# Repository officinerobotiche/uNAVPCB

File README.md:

# ![Officine Robotiche][Logo] &micro;Nav PCB
**The first DC motor board in 4cm X 4cm** - PCB boards for &micro;Nav

This is a project in development by [Officine Robotiche] team, the check info at [official &micro;Nav site](http://unav.officinerobotiche.it/).

Feel free to ask for help, submit suggestions, satisfy your curiosity on our [**Users Group**](https://groups.google.com/forum/?hl=it#!forum/unav-users)

###Join on open firmware project [uNAV.X](https://github.com/officinerobotiche/uNAV.X)!!!

# Hardware features
- 2 DC motor control (external encoders and double H-bridge are required)
- size: 4cm x 4cm
- Matrix board with holes 2.54mm compliant
- Free 256Kb EEPROM in I2C 
- Voltage input *(Max 23V to 6V)*
- 2 internal regulators:
  - External input -> 5V
  - 5V -> 3.3V
- 4 LEDs
- ICSP programming

## DC Motor control
- 2 PWM outputs to control the speed of the motors
- Encoder input. *You can select 5V input or 3.3V to power on your encoders*: 
  - 2 channels (A, B)
  - 3 channels (A, B and Z axis)
- Analog input for current sensing
- Analog input for temperature sensing
- Pin to enable H-Bridge

## Communications
- 2 serial ports
- 1 I2C port
- 7 GP I/O (You can add feature remapping pins) 
 
# Available Shields
- [&micro;Bridge](https://github.com/officinerobotiche/uBridgePCB)

# Graphical tool for PID tuning
- [uNav_PID_Tuner](https://github.com/officinerobotiche/uNav_PID_Tuner)

[Officine Robotiche]:http://www.officinerobotiche.it/
[Logo]:http://2014.officinerobotiche.it/wp-content/uploads/sites/4/2014/09/ORlogoSimpleSmall.png

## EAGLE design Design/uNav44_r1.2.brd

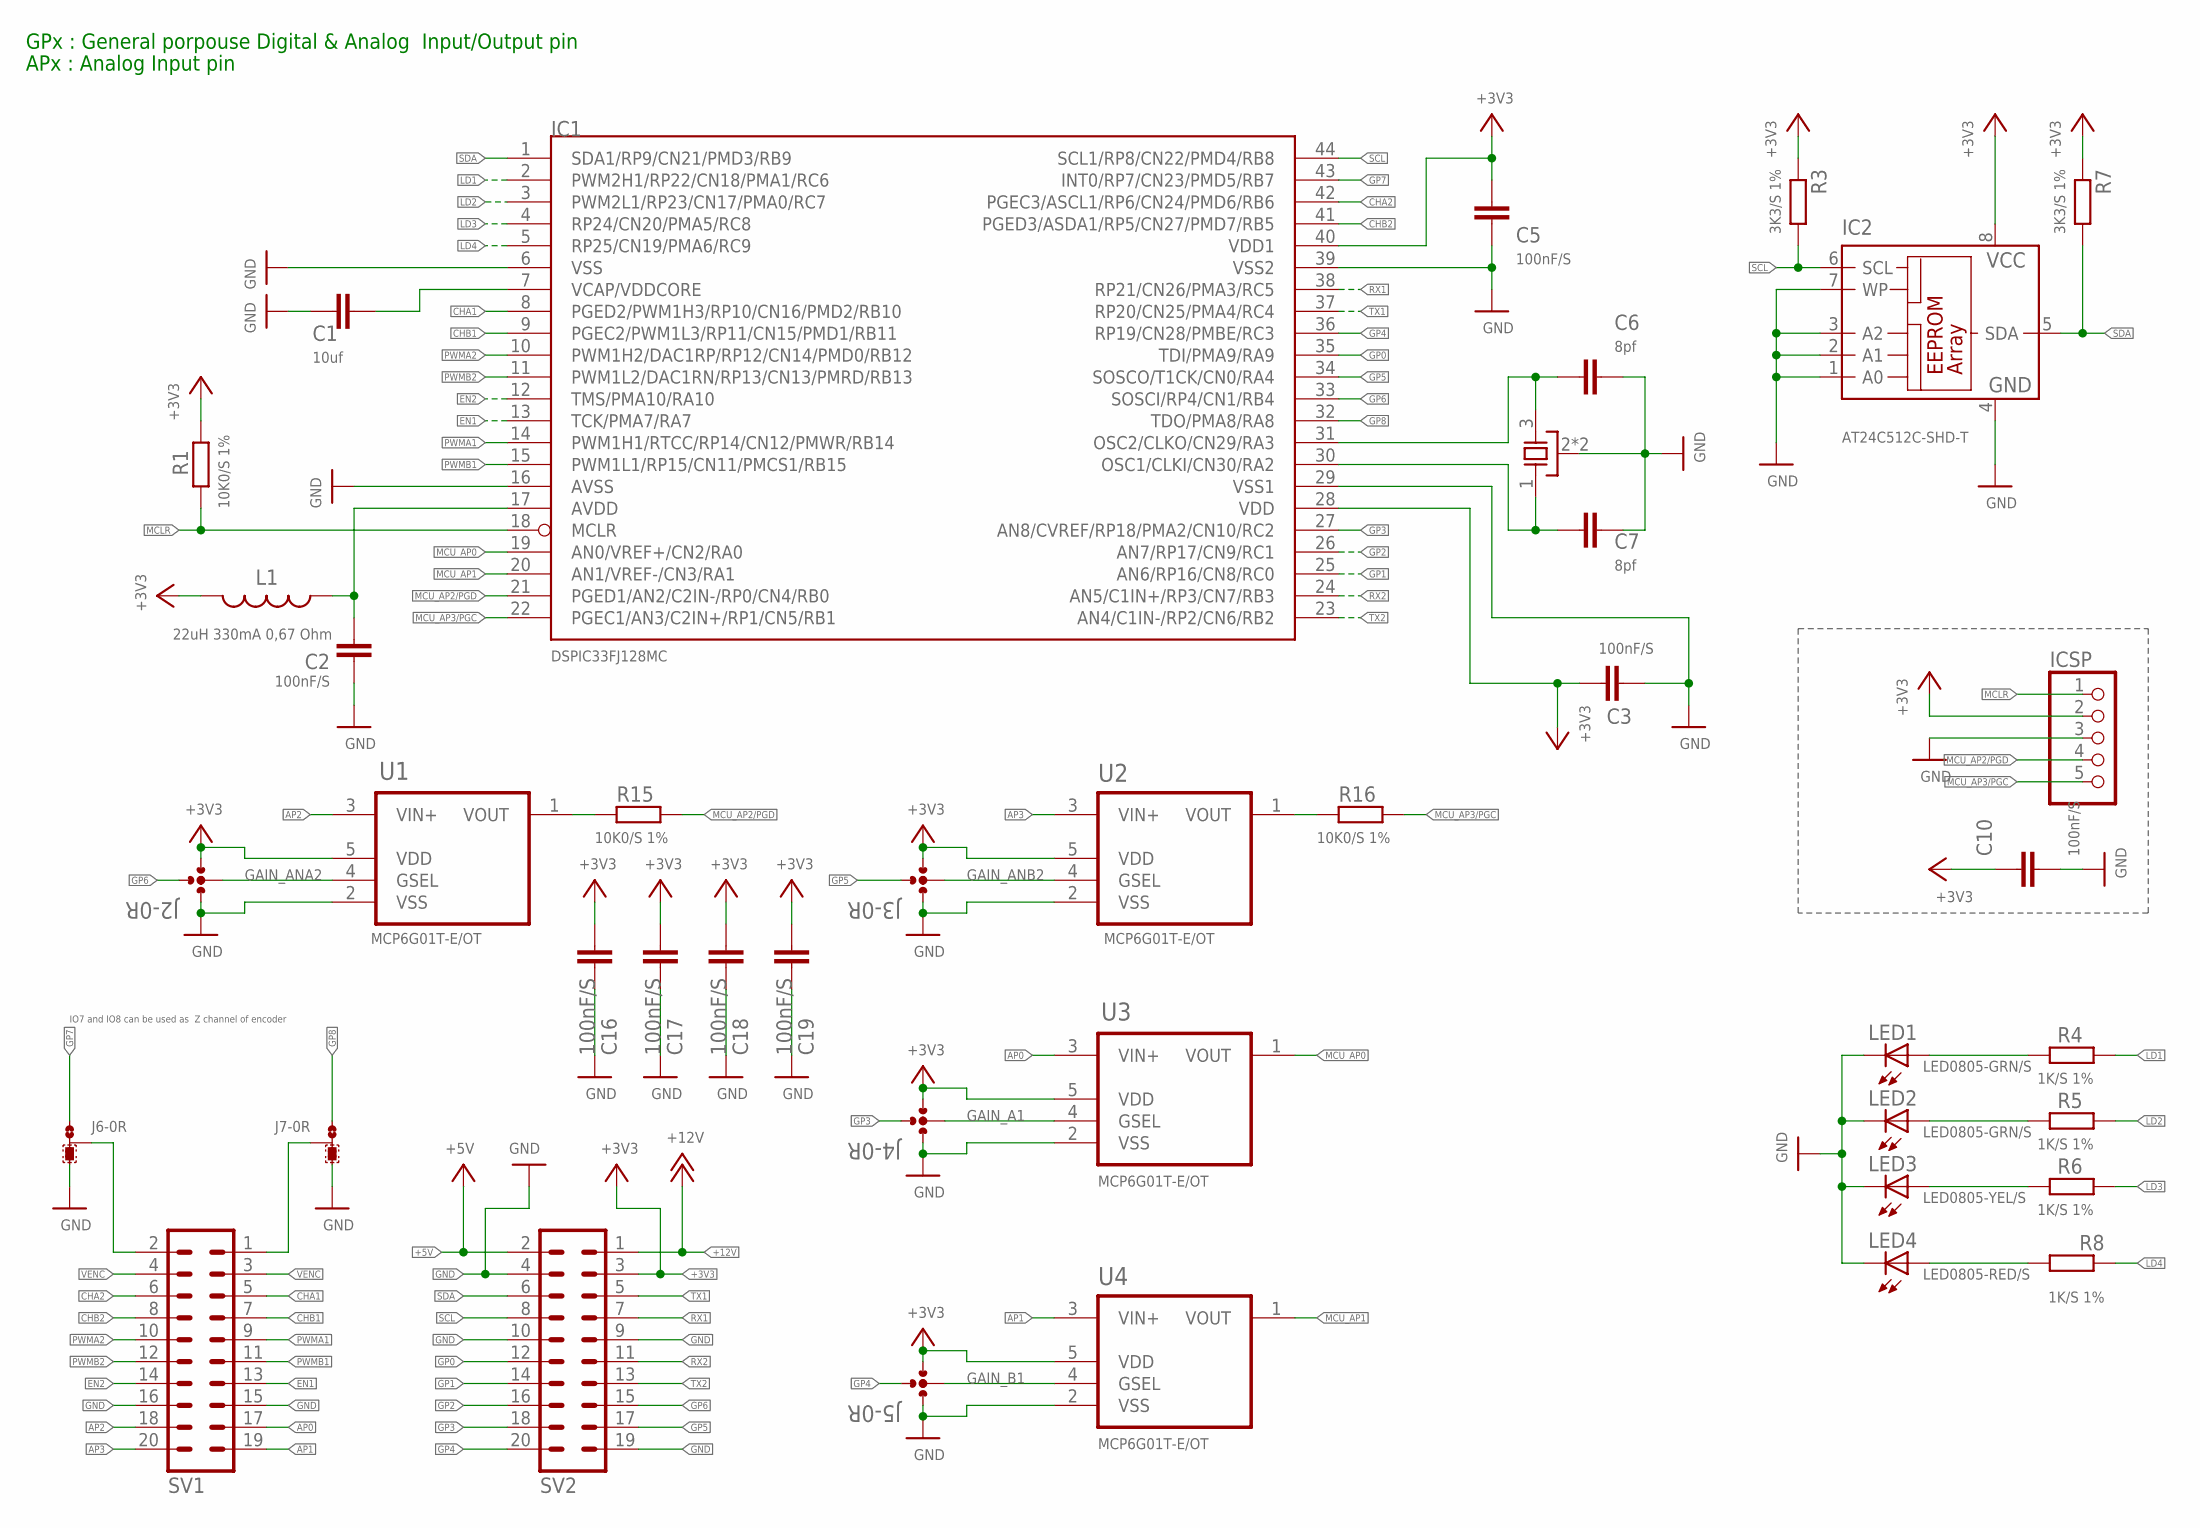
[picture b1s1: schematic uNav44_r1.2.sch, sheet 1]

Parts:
C1: 10uf; C1206
C2, C3, C5, C10, C16, C17, C18, C19: 100nF/S; C0603
C6, C7: 8pf; C0603
IC1: DSPIC33FJ128MC; TQFP44
IC2: AT24C512C-SHD-T; SO-08M
ICSP: PINHD-1X05_2.54-S; 1X05-S
J2, J3, J4, J5: 0R-JUMP-4; C0R-JUMP-4
J6, J7: 0R-JUMPC; C0R-JMP
L1: 22uH 330mA 0,67 Ohm; 0805
LED1, LED2: LED0805-GRN/S; CHIPLED_0805
LED3: LED0805-YEL/S; CHIPLED_0805
LED4: LED0805-RED/S; CHIPLED_0805
R1, R15, R16: 10K0/S 1%; R0603
R3, R7: 3K3/S 1%; R0603
R4, R5, R6, R8: 1K/S 1%; R0603
SV1, SV2: MA10-2
U1, U2, U3, U4: MCP6G01T-E/OT; SOT95P300X145-5N
XT1: 10Mhz 8pf SMD 3,20x2,50; CTS_32X25

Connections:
+3V3: C3.1, C5.2, C10.1, C16.1, C17.1, C18.1, C19.1, IC1.28 (VDD), IC1.40 (VDD1), IC2.8 (VCC), ICSP.2, J2.1, J3.1, J4.1, J5.1, L1.2, R1.2, R3.1, R7.1, SV2.3, U1.5 (VDD), U2.5 (VDD), U3.5 (VDD), U4.5 (VDD); also elsewhere on the board
+5V: SV2.2; also elsewhere on the board
+12V: SV2.1; also elsewhere on the board
AP0: SV1.17, U3.3 (VIN+)
AP1: SV1.19, U4.3 (VIN+)
AP2: SV1.18, U1.3 (VIN+)
AP3: SV1.20, U2.3 (VIN+)
AVDD: C2.2, IC1.17 (AVDD), L1.1
CHA1: IC1.8 (PGED2/PWM1H3/RP10/CN16/PMD2/RB10), SV1.5
CHA2: IC1.42 (PGEC3/ASCL1/RP6/CN24/PMD6/RB6), SV1.6
CHB1: IC1.9 (PGEC2/PWM1L3/RP11/CN15/PMD1/RB11), SV1.7
CHB2: IC1.41 (PGED3/ASDA1/RP5/CN27/PMD7/RB5), SV1.8
EN1: IC1.13 (TCK/PMA7/RA7), SV1.13
EN2: IC1.12 (TMS/PMA10/RA10), SV1.14
GAIN_A1: J4.2, U3.4 (GSEL)
GAIN_ANA2: J2.2, U1.4 (GSEL)
GAIN_ANB2: J3.2, U2.4 (GSEL)
GAIN_B1: J5.2, U4.4 (GSEL)
GND: C1.2, C2.1, C3.2, C5.1, C6.2, C7.1, C10.2, C16.2, C17.2, C18.2, C19.2, IC1.6 (VSS), IC1.16 (AVSS), IC1.29 (VSS1), IC1.39 (VSS2), IC2.1 (A0), IC2.2 (A1), IC2.3 (A2), IC2.4 (GND), IC2.7 (WP), ICSP.3, J2.3, J3.3, J4.3, J5.3, J6.3, J7.3, LED1.C, LED2.C, LED3.C, LED4.C, SV1.15, SV1.16, SV2.4, SV2.9, SV2.10, SV2.19, U1.2 (VSS), U2.2 (VSS), U3.2 (VSS), U4.2 (VSS), XT1.2 (GND), XT1.4 (GND); also elsewhere on the board
GP0: IC1.35 (TDI/PMA9/RA9), SV2.12
GP1: IC1.25 (AN6/RP16/CN8/RC0), SV2.14
GP2: IC1.26 (AN7/RP17/CN9/RC1), SV2.16
GP3: IC1.27 (AN8/CVREF/RP18/PMA2/CN10/RC2), J4.4, SV2.18
GP4: IC1.36 (RP19/CN28/PMBE/RC3), J5.4, SV2.20
GP5: IC1.34 (SOSCO/T1CK/CN0/RA4), J3.4, SV2.17
GP6: IC1.33 (SOSCI/RP4/CN1/RB4), J2.4, SV2.15
GP7: IC1.43 (INT0/RP7/CN23/PMD5/RB7), J6.1
GP8: IC1.32 (TDO/PMA8/RA8), J7.1
LD1: IC1.2 (PWM2H1/RP22/CN18/PMA1/RC6), R4.1
LD2: IC1.3 (PWM2L1/RP23/CN17/PMA0/RC7), R5.1
LD3: IC1.4 (RP24/CN20/PMA5/RC8), R6.1
LD4: IC1.5 (RP25/CN19/PMA6/RC9), R8.1
MCLR: IC1.18 (MCLR), ICSP.1, R1.1
MCU_AP0: IC1.19 (AN0/VREF+/CN2/RA0), U3.1 (VOUT)
MCU_AP1: IC1.20 (AN1/VREF-/CN3/RA1), U4.1 (VOUT)
MCU_AP2/PGD: IC1.21 (PGED1/AN2/C2IN-/RP0/CN4/RB0), ICSP.4, R15.1
MCU_AP3/PGC: IC1.22 (PGEC1/AN3/C2IN+/RP1/CN5/RB1), ICSP.5, R16.1
unnamed: C7.2, IC1.30 (OSC1/CLKI/CN30/RA2), XT1.1 (X1)
unnamed: C6.1, IC1.31 (OSC2/CLKO/CN29/RA3), XT1.3 (X2)
unnamed: J6.2, SV1.2
unnamed: LED1.A, R4.2
unnamed: LED2.A, R5.2
unnamed: R15.2, U1.1 (VOUT)
unnamed: R16.2, U2.1 (VOUT)
unnamed: J7.2, SV1.1
PWMA1: IC1.14 (PWM1H1/RTCC/RP14/CN12/PMWR/RB14), SV1.9
PWMA2: IC1.10 (PWM1H2/DAC1RP/RP12/CN14/PMD0/RB12), SV1.10
PWMB1: IC1.15 (PWM1L1/RP15/CN11/PMCS1/RB15), SV1.11
PWMB2: IC1.11 (PWM1L2/DAC1RN/RP13/CN13/PMRD/RB13), SV1.12
RX1: IC1.38 (RP21/CN26/PMA3/RC5), SV2.7
RX2: IC1.24 (AN5/C1IN+/RP3/CN7/RB3), SV2.11
SCL: IC1.44 (SCL1/RP8/CN22/PMD4/RB8), IC2.6 (SCL), R3.2, SV2.8
SDA: IC1.1 (SDA1/RP9/CN21/PMD3/RB9), IC2.5 (SDA), R7.2, SV2.6
TX1: IC1.37 (RP20/CN25/PMA4/RC4), SV2.5
TX2: IC1.23 (AN4/C1IN-/RP2/CN6/RB2), SV2.13
VCAP/VDDCORE: C1.1, IC1.7 (VCAP/VDDCORE)
VENC: SV1.3, SV1.4; also elsewhere on the board
VENC1-LD3: LED3.A, R6.2
VENC2-LD4: LED4.A, R8.2

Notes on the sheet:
IO7 and IO8 can be used as Z channel of encoder
GPx : General porpouse Digital & Analog Input/Output pin
APx : Analog Input pin

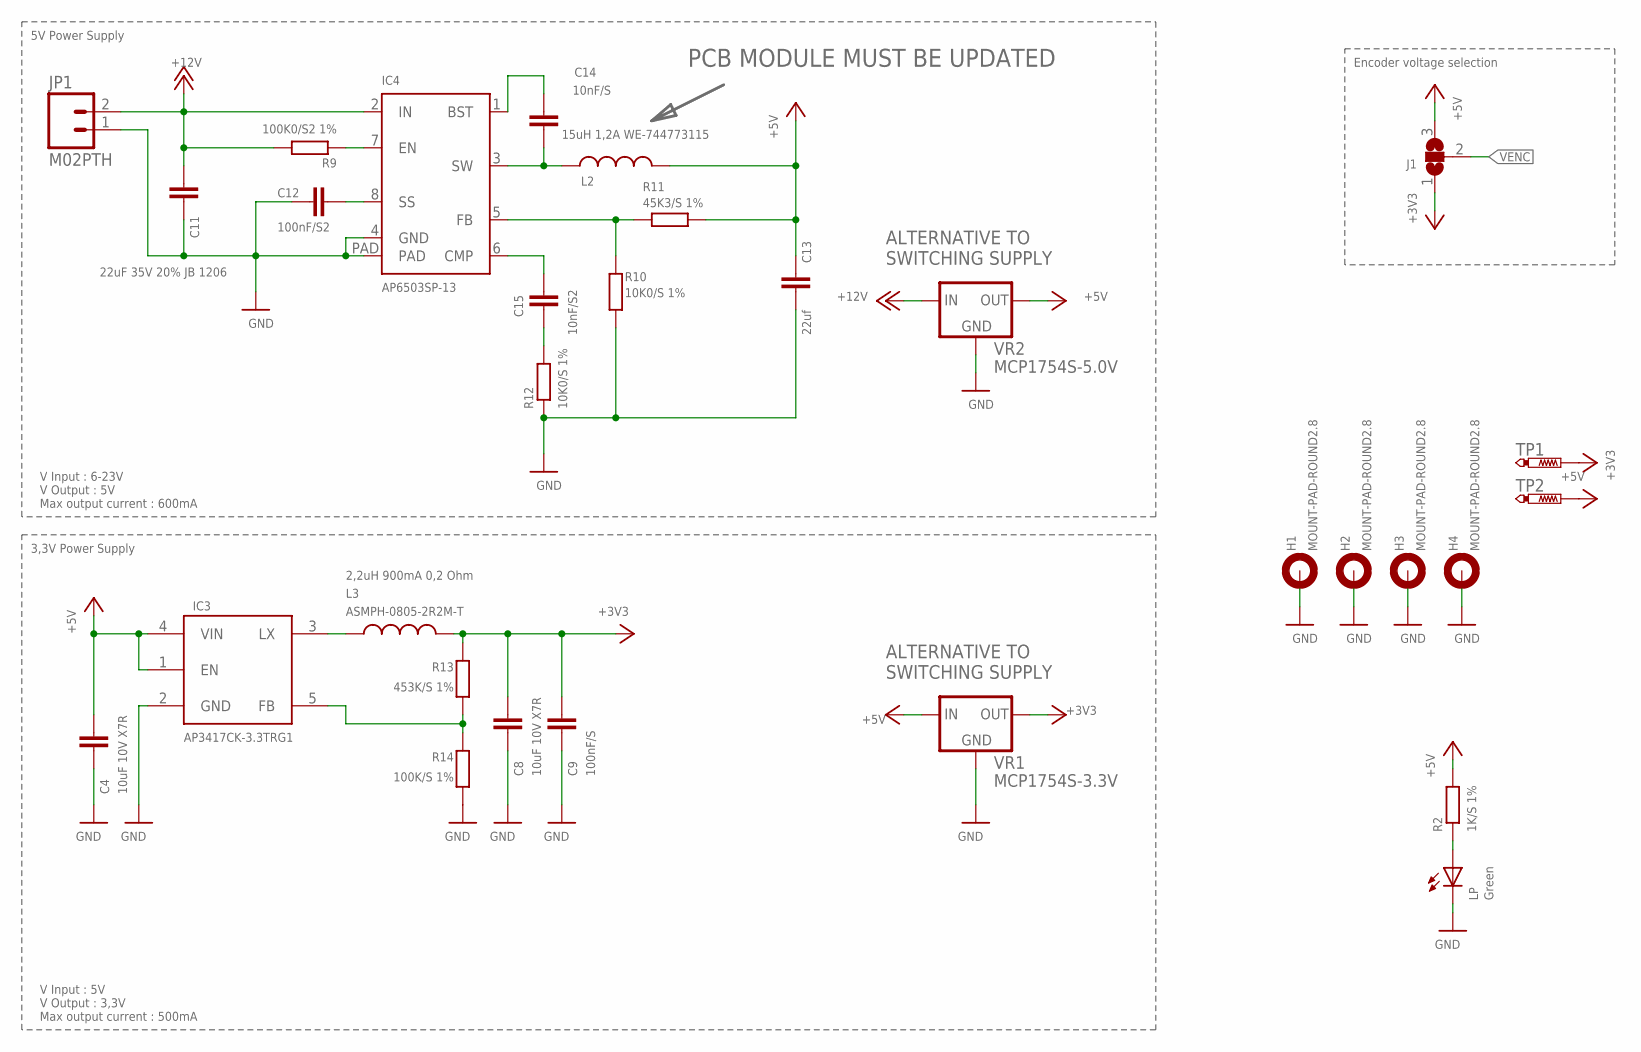
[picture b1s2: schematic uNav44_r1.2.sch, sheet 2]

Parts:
C4, C8: 10uF 10V X7R; C0805
C9: 100nF/S; C0603
C11: 22uF 35V 20% JB 1206; C1206
C12: 100nF/S2; C0603
C13: 22uf; C1206
C14: 10nF/S; C0603
C15: 10nF/S2; C0603
H1, H2, H3, H4: MOUNT-PAD-ROUND2.8; 2,8-PAD
IC3: AP3417CK-3.3TRG1; SOT-23-5
IC4: AP6503SP-13; SO-8EP
J1: SJ2W; SJ_2
JP1: M02PTH; 1X02
L2: 15uH 1,2A WE-744773115; 1210
L3: ASMPH-0805-2R2M-T; 0805
LP: Green; CHIPLED_0805
R2: 1K/S 1%; R0603
R9: 100K0/S2 1%; R0603
R10, R12: 10K0/S 1%; R0603
R11: 45K3/S 1%; R0603
R13: 453K/S 1%; R0603
R14: 100K/S 1%; R0603
TP1, TP2: PTR1TP07R; TP07R
VR1: MCP1754S-3.3V; SOT89
VR2: MCP1754S-5.0V; SOT89

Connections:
+3V3: C8.1, C9.1, J1.1, L3.2, R13.2, TP1.TP, VR1.3 (OUT); also elsewhere on the board
+5V: C4.1, C13.1, IC3.1 (EN), IC3.4 (VIN), J1.3, L2.2, R2.2, R11.2, TP2.TP, VR1.1 (IN), VR2.3 (OUT); also elsewhere on the board
+12V: C11.1, IC4.2 (IN), JP1.2, R9.2, VR2.1 (IN); also elsewhere on the board
GND: C4.2, C8.2, C9.2, C11.2, C12.2, C13.2, H1.B2,8, H2.B2,8, H3.B2,8, H4.B2,8, IC3.2 (GND), IC4.4 (GND), IC4.PAD, JP1.1, LP.C, R10.2, R12.1, R14.1, VR1.2 (GND), VR1.4 (GND), VR2.2 (GND), VR2.4 (GND); also elsewhere on the board
unnamed: IC3.3 (LX), L3.1
unnamed: C14.1, IC4.1 (BST)
unnamed: LP.A, R2.1
unnamed: IC4.7 (EN), R9.1
unnamed: IC3.5 (FB), R13.1, R14.2
unnamed: C12.1, IC4.8 (SS)
unnamed: IC4.5 (FB), R10.1, R11.1
unnamed: C14.2, IC4.3 (SW), L2.1
unnamed: C15.1, IC4.6 (CMP)
unnamed: C15.2, R12.2
VENC: J1.2; also elsewhere on the board

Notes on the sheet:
2,2uH 900mA 0,2 Ohm
Encoder voltage selection
5V Power Supply
V Input : 6-23V V Output : 5V Max output current : 600mA
3,3V Power Supply
V Input : 5V V Output : 3,3V Max output current : 500mA
ALTERNATIVE TO SWITCHING SUPPLY
PCB MODULE MUST BE UPDATED

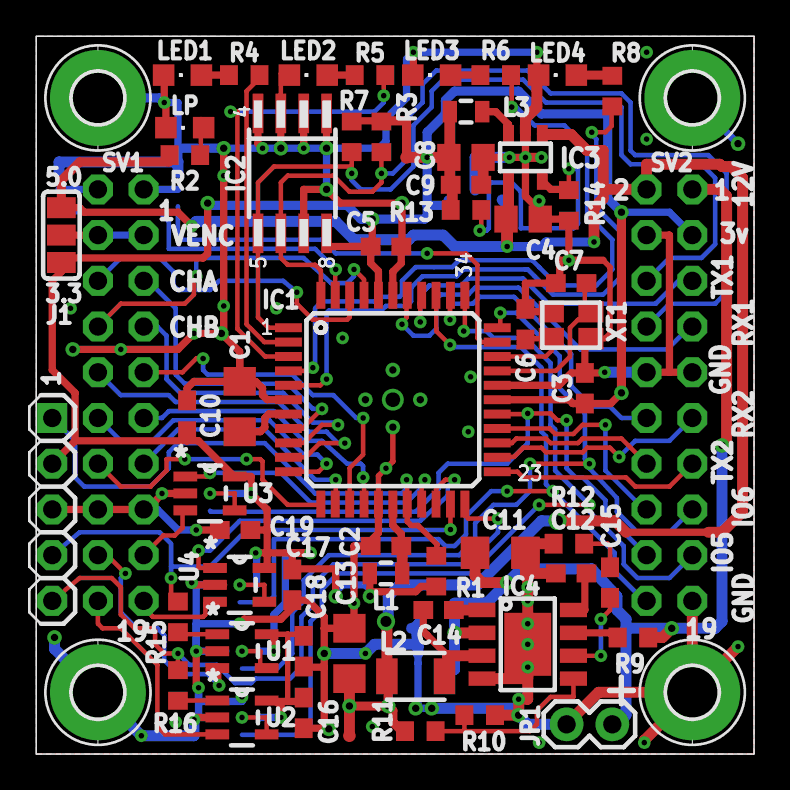
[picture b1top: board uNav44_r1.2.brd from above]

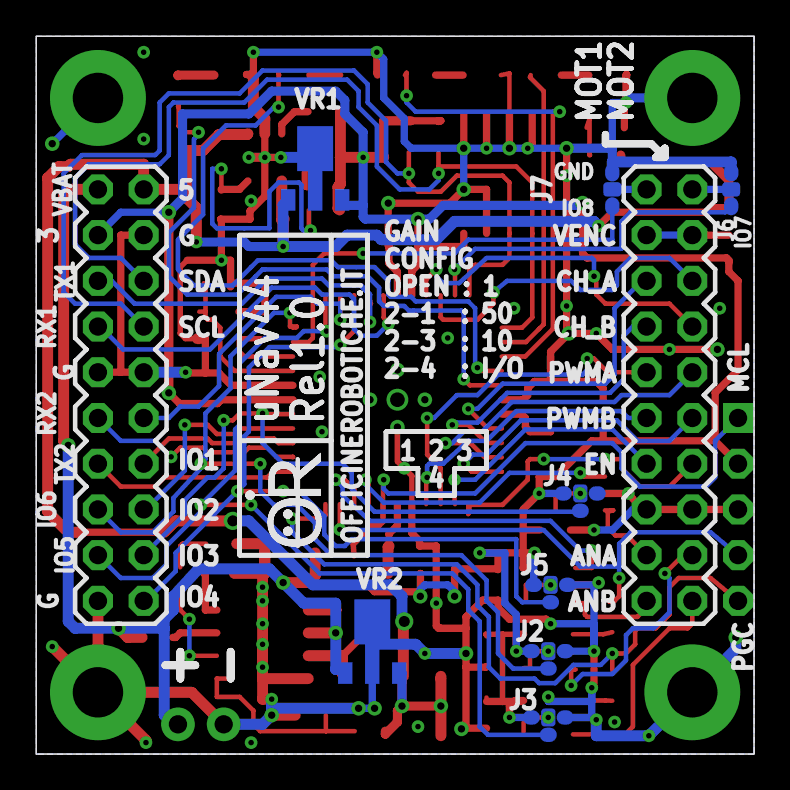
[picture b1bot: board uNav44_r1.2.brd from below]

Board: 2 copper layers, 39.9 x 39.9 mm, 71 parts (10 on the bottom side), 69 nets.

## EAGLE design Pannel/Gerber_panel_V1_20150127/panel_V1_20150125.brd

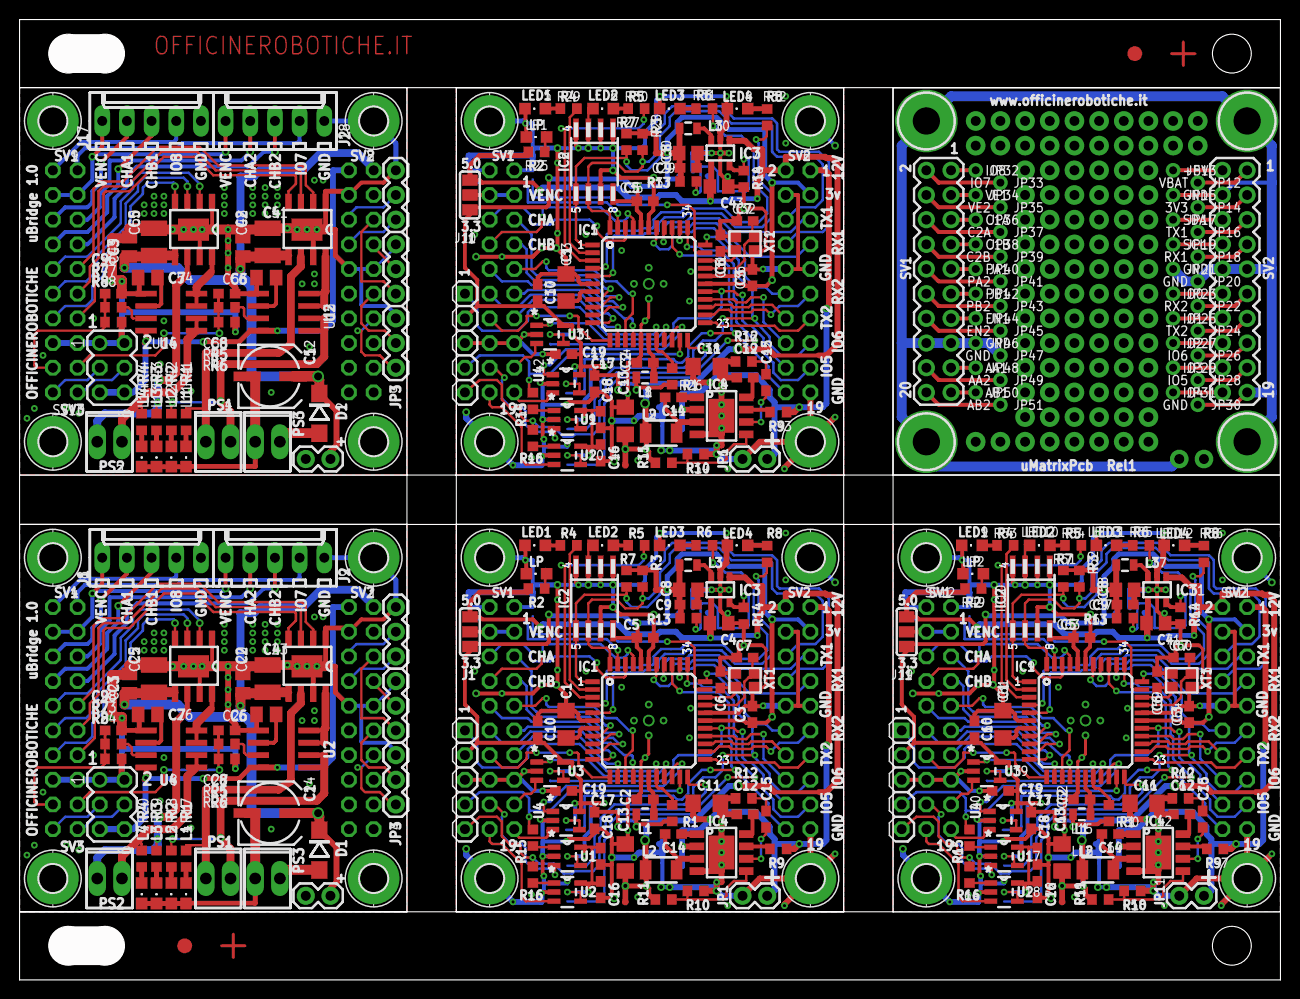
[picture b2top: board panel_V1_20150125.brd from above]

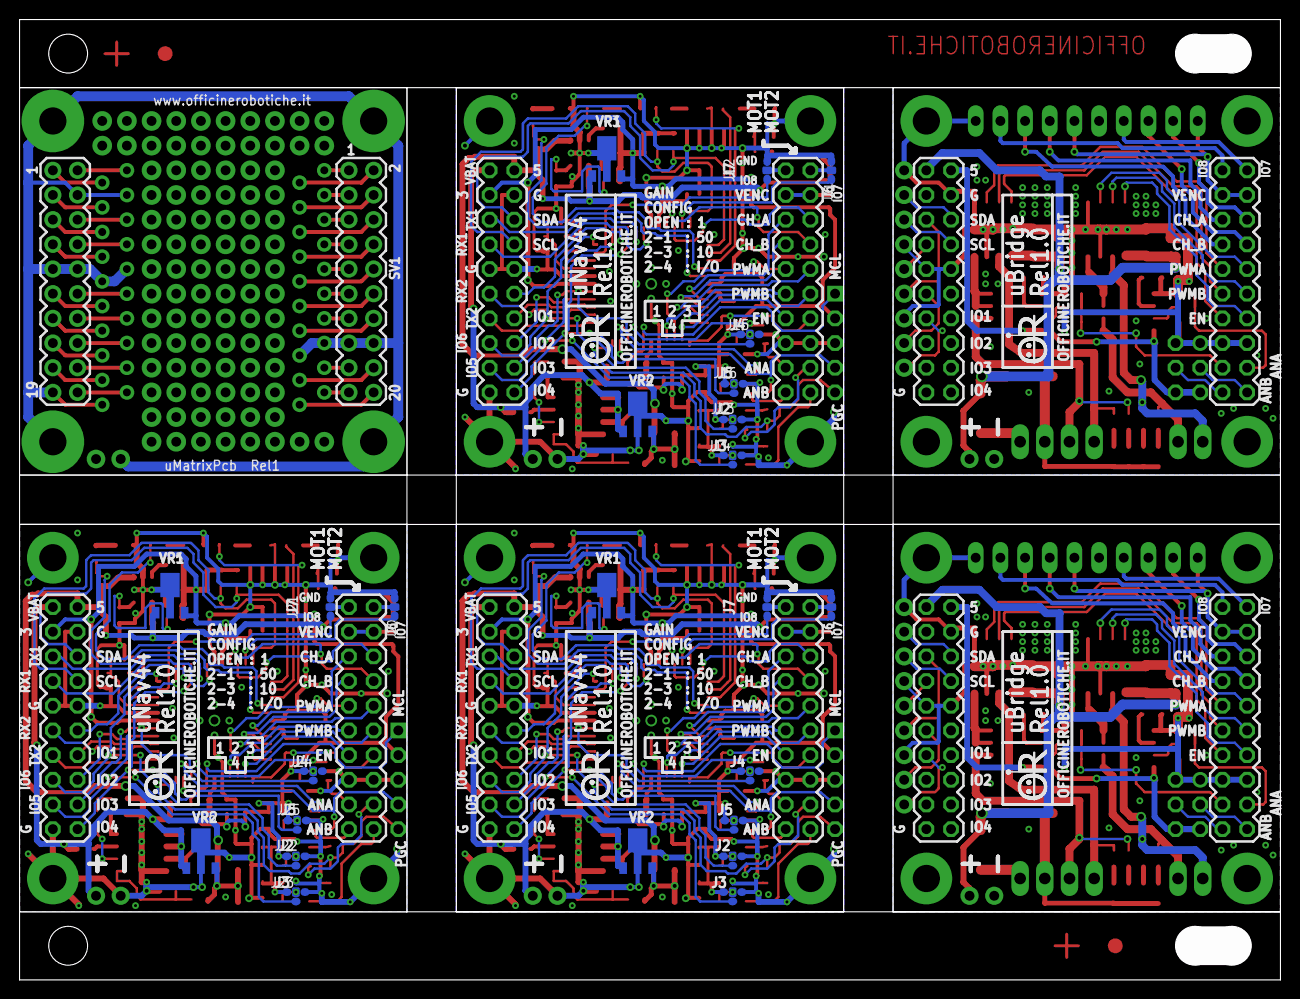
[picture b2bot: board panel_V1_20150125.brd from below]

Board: 2 copper layers, 129.8 x 98.9 mm, 338 parts (34 on the bottom side), 324 nets.

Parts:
C1, C33, C61: 10uf; C1206
C2, C3, C5, C9, C10, C16, C17, C18, C19, C29, C34, C35, C36, C37, C44, C45, C46, C47, C57, C62, C63, C64, C65, C72, C73, C74, C75: 100nF/S; C0603
C4, C8, C30, C43, C58, C71: 10uF 10V X7R; C0805
C6, C7, C31, C32, C59, C60: 18pf; C0603
C11, C38, C66: 22uF 35V 20% JB 1206; C1206
C12, C27, C28, C39, C55, C56, C67: 100nF/S2; C0603
C13, C40, C68: 22uf; C1206
C14, C41, C69: 10nF/S; C0603
C15, C42, C70: 10nF/S2; C0603
C20, C21, C48, C49: 220nF; C0805K
C22, C23, C50, C51: 10uF/S6 50V; C3225
C24, C52: PCE4554CT-ND; UD-6,3X7,7_NICHICON
C25, C26, C53, C54: 1nF; C0805K
D1, D2: ES1G-E2; DO214BA
H1, H2, H3, H4, H5, H6, H7, H8, H9, H10, H11, H12, H13, H14, H15, H16, H17, H18, H19, H20: MOUNT-PAD-ROUND2.8; 2,8-PAD
IC1, IC5, IC9: DSPIC33FJ128MC; TQFP44
IC2, IC6, IC10: 24LC024; SO-08M
IC3, IC7, IC11: AP3417CK-3.3TRG1; SOT-23-5
IC4, IC8, IC12: AP6503SP-13; SO-8EP
ICSP, ICSP1, ICSP2: 1X05-S
J1, J10, J19: SJ_2
J2, J3, J4, J5, J13, J14, J15, J16, J22, J23, J24, J25: C0R-JUMP-4
J6, J7, J11, J12, J20, J21: 0R-JUMPC; C0R-JMP
J8, J9, J17, J18: 22-27-2051-05; 6410-05
JP1, JP2, JP6, JP7, JP11: M02PTH; 1X02
JP3, JP4, JP5, JP8, JP9, JP10: 1X03
JP12, JP13, JP14, JP15, JP16, JP17, JP18, JP19, JP20, JP21, JP22, JP23, JP24, JP25, JP26, JP27, JP28, JP29, JP30, JP31, JP32, JP33, JP34, JP35, JP36, JP37, JP38, JP39, JP40, JP41, JP42, JP43, JP44, JP45, JP46, JP47, JP48, JP49, JP50, JP51: M01PTH_1.27MM_TESTPOINT; 1X0.127_TESTPOINT
L1, L8, L15: 22 uH; 0805
L2, L9, L16: 10uH_520mA; 1210
L3, L10, L17: ASMPH-0805-2R2M-T; 0805
L4, L6, L11, L13: LED0805-YEL/S; CHIPLED_0805
L5, L7, L12, L14: LED0805-GRN/S; CHIPLED_0805
LED1, LED2, LED5, LED6, LED9, LED10: LED0805-GRN/S; CHIPLED_0805
LED3, LED7, LED11: LED0805-YEL/S; CHIPLED_0805
LED4, LED8, LED12: LED0805-RED/S; CHIPLED_0805
LP, LP1, LP2: Green; CHIPLED_0805
PS1, PS2, PS3, PS4, PS5, PS6: 2POL254
R1, R10, R12, R15, R16, R26, R34, R36, R39, R40, R50, R58, R60, R63, R64: 10K0/S 1%; R0603
R2, R4, R5, R6, R8, R17, R18, R19, R20, R25, R29, R30, R31, R32, R41, R42, R43, R44, R49, R53, R54, R55, R56: 1K/S 1%; R0603
R3, R7, R22, R24, R27, R28, R46, R48, R51, R52: 3K3/S 1%; R0603
R9, R33, R57: 100K0/S2 1%; R0603
R11, R35, R59: 45K3/S 1%; R0603
R13, R37, R61: 450K/S 1%; R0603
R14, R38, R62: 100K/S 1%; R0603
R21, R23, R45, R47: 6K49/S 1%; R0603
SV1, SV2, SV3, SV4, SV6, SV7, SV8, SV9, SV11, SV12: MA10-2
SV5, SV10: MA03-2
TP1, TP2, TP3, TP4, TP5, TP6: PTR1TP07R; TP07R
U1, U2, U3, U4, U9, U10, U11, U12, U17, U18, U19, U20: MCP6G01T-E/OT; SOT95P300X145-5N
U5, U6, U13, U14: A4950; 8SOICN
U7, U8, U15, U16: ACS723; SO08
UN1: UNAV_BOARD
VR1, VR3, VR5: MCP1754S-3.3V; SOT89
VR2, VR4, VR6: MCP1754S-5.0V; SOT89
XT1, XT2, XT3: CTS_32X25

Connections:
+3V2: C29.1, C30.1, C35.2, C36.1, C37.1, C44.1, C45.1, C46.1, C47.1, IC5.28, IC5.40, IC6.8, ICSP1.2, J10.1, J13.1, J14.1, J15.1, J16.1, L8.2, L10.2, R26.2, R27.1, R28.1, R37.2, SV6.3, TP3.TP, U9.5, U10.5, U11.5, U12.5, VR3.3
+3V3: C3.1, C5.2, C8.1, C9.1, C10.1, C16.1, C17.1, C18.1, C19.1, IC1.28, IC1.40, IC2.8, ICSP.2, J1.1, J2.1, J3.1, J4.1, J5.1, L1.2, L3.2, R1.2, R3.1, R7.1, R13.2, SV2.3, TP1.TP, U1.5, U2.5, U3.5, U4.5, VR1.3
+3V5: C57.1, C58.1, C63.2, C64.1, C65.1, C72.1, C73.1, C74.1, C75.1, IC9.28, IC9.40, IC10.8, ICSP2.2, J19.1, J22.1, J23.1, J24.1, J25.1, L15.2, L17.2, R50.2, R51.1, R52.1, R61.2, SV11.3, TP5.TP, U17.5, U18.5, U19.5, U20.5, VR5.3
+3V6: JP14.1, UN1.+3V3
+5V: C4.1, C13.1, IC3.1, IC3.4, J1.3, L2.2, R2.2, R11.2, SV2.2, TP2.TP, VR1.1, VR2.3
+5V1: SV3.2, SV5.5, SV5.6, U7.8, U8.8
+5V2: C40.1, C43.1, IC7.1, IC7.4, J10.3, L9.2, R25.2, R35.2, SV6.2, TP4.TP, VR3.1, VR4.3
+5V3: SV8.2, SV10.5, SV10.6, U15.8, U16.8
+5V4: C68.1, C71.1, IC11.1, IC11.4, J19.3, L16.2, R49.2, R59.2, SV11.2, TP6.TP, VR5.1, VR6.3
+5V5: JP13.1, UN1.+5V
+12V: C11.1, IC4.2, JP1.2, R9.2, SV2.1, VR2.1
+12V1: C20.2, C21.2, C22.2, C23.2, C24.+, D1.C, JP2.2, SV3.1, U5.5, U6.5
+12V2: C38.1, IC8.2, JP6.2, R33.2, SV6.1, VR4.1
+12V3: C48.2, C49.2, C50.2, C51.2, C52.+, D2.C, JP7.2, SV8.1, U13.5, U14.5
+12V4: C66.1, IC12.2, JP11.2, R57.2, SV11.1, VR6.1
+12V5: JP12.1, UN1.VBAT
ANA1: IC1.19, U3.1
ANA2: SV1.18, U1.3
ANA2/PGD: IC1.21, ICSP.4, R15.1
ANA2/PGD1: IC5.21, ICSP1.4, R39.1
ANA2/PGD2: IC9.21, ICSP2.4, R63.1
ANA3: C27.1, R21.1, R22.2, SV4.17
ANA4: C28.1, R23.1, R24.2, SV4.18
ANA5: IC5.19, U11.1
ANA6: SV7.18, U9.3
ANA7: C55.1, R45.1, R46.2, SV9.17
ANA8: C56.1, R47.1, R48.2, SV9.18
ANA9: IC9.19, U19.1
ANA10: SV12.18, U17.3
ANA11: JP49.1, UN1.ANA2
ANB1: IC1.20, U4.1
ANB2: SV1.20, U2.3
ANB2/PGC: IC1.22, ICSP.5, R16.1
ANB2/PGC1: IC5.22, ICSP1.5, R40.1
ANB2/PGC2: IC9.22, ICSP2.5, R64.1
ANB3: SV4.19, SV5.4
ANB4: SV4.20, SV5.3
ANB5: IC5.20, U12.1
ANB6: SV7.20, U10.3
ANB7: SV9.19, SV10.4
ANB8: SV9.20, SV10.3
ANB9: IC9.20, U20.1
ANB10: SV12.20, U18.3
ANB11: JP51.1, UN1.ANB2
AVDD: C2.2, IC1.17, L1.1
AVDD1: C34.2, IC5.17, L8.1
AVDD2: C62.2, IC9.17, L15.1
CHA1: IC1.8, SV1.5
CHA2: IC1.42, SV1.6
CHA3: J9.4, SV4.5
CHA4: J8.4, SV4.6
CHA5: IC5.8, SV7.5
CHA6: IC5.42, SV7.6
CHA7: J18.4, SV9.5
CHA8: J17.4, SV9.6
CHA9: IC9.8, SV12.5
CHA10: IC9.42, SV12.6
CHA11: JP36.1, UN1.CH1A
CHA12: JP37.1, UN1.CH2A
CHB1: IC1.9, SV1.7
CHB2: IC1.41, SV1.8
CHB3: J9.3, SV4.7
CHB4: J8.3, SV4.8
CHB5: IC5.9, SV7.7
CHB6: IC5.41, SV7.8
CHB7: J18.3, SV9.7
CHB8: J17.3, SV9.8
CHB9: IC9.9, SV12.7
CHB10: IC9.41, SV12.8
CHB11: JP38.1, UN1.CH1B
CHB12: JP39.1, UN1.CH2B
EN1: IC1.13, SV1.13
EN2: IC1.12, SV1.14
EN3: SV4.13, U5.4
EN4: SV4.14, U6.4
EN5: IC5.13, SV7.13
EN6: IC5.12, SV7.14
EN7: SV9.13, U13.4
EN8: SV9.14, U14.4
EN9: IC9.13, SV12.13
EN10: IC9.12, SV12.14
EN11: JP44.1, UN1.EN1
EN12: JP45.1, UN1.EN2
GAIN_A1: J4.2, U3.4
GAIN_A2: J15.2, U11.4
GAIN_A3: J24.2, U19.4
GAIN_ANA1: J13.2, U9.4
GAIN_ANA2: J2.2, U1.4
GAIN_ANA3: J22.2, U17.4
GAIN_ANB1: J14.2, U10.4
GAIN_ANB2: J3.2, U2.4
GAIN_ANB3: J23.2, U18.4
GAIN_B1: J5.2, U4.4
GAIN_B2: J16.2, U12.4
GAIN_B3: J25.2, U20.4
GND: C1.2, C2.1, C3.2, C4.2, C5.1, C6.2, C7.1, C8.2, C9.2, C10.2, C11.2, C12.2, C13.2, C16.2, C17.2, C18.2, C19.2, H1.B2,8, H2.B2,8, H3.B2,8, H4.B2,8, IC1.6, IC1.16, IC1.29, IC1.39, IC2.1, IC2.2, IC2.3, IC2.4, IC2.7, IC3.2, IC4.4, IC4.PAD, ICSP.3, J2.3, J3.3, J4.3, J5.3, J6.3, J7.3, JP1.1, LED1.C, LED2.C, LED3.C, LED4.C, LP.C, R10.2, R12.1, R14.1, SV1.15, SV1.16, SV2.4, SV2.9, SV2.10, SV2.19, U1.2, U2.2, U3.2, U4.2, VR1.2, VR1.4, VR2.2, VR2.4, XT1.2, XT1.4
GND1: C20.1, C21.1, C22.1, C23.1, C24.-, C25.2, C26.2, C27.2, C28.2, H5.B2,8, H6.B2,8, H7.B2,8, H8.B2,8, J8.1, J9.1, JP2.1, JP3.3, JP4.3, JP5.3, L4.C, L5.C, L6.C, L7.C, PS3.1, R22.1, R24.1, SV3.4, SV3.9, SV3.10, SV3.19, SV4.15, SV4.16, SV5.1, SV5.2, U5.1, U5.7, U5.PAD, U6.1, U6.7, U6.PAD, U7.5, U8.5
GND2: C29.2, C30.2, C31.2, C32.1, C33.2, C34.1, C35.1, C36.2, C37.2, C38.2, C39.2, C40.2, C43.2, C44.2, C45.2, C46.2, C47.2, H9.B2,8, H10.B2,8, H11.B2,8, H12.B2,8, IC5.6, IC5.16, IC5.29, IC5.39, IC6.1, IC6.2, IC6.3, IC6.4, IC6.7, IC7.2, IC8.4, IC8.PAD, ICSP1.3, J11.3, J12.3, J13.3, J14.3, J15.3, J16.3, JP6.1, LED5.C, LED6.C, LED7.C, LED8.C, LP1.C, R34.2, R36.1, R38.1, SV6.4, SV6.9, SV6.10, SV6.19, SV7.15, SV7.16, U9.2, U10.2, U11.2, U12.2, VR3.2, VR3.4, VR4.2, VR4.4, XT2.2, XT2.4
GND3: C48.1, C49.1, C50.1, C51.1, C52.-, C53.2, C54.2, C55.2, C56.2, H13.B2,8, H14.B2,8, H15.B2,8, H16.B2,8, J17.1, J18.1, JP7.1, JP8.3, JP9.3, JP10.3, L11.C, L12.C, L13.C, L14.C, PS6.1, R46.1, R48.1, SV8.4, SV8.9, SV8.10, SV8.19, SV9.15, SV9.16, SV10.1, SV10.2, U13.1, U13.7, U13.PAD, U14.1, U14.7, U14.PAD, U15.5, U16.5
GND4: C57.2, C58.2, C59.2, C60.1, C61.2, C62.1, C63.1, C64.2, C65.2, C66.2, C67.2, C68.2, C71.2, C72.2, C73.2, C74.2, C75.2, H17.B2,8, H18.B2,8, H19.B2,8, H20.B2,8, IC9.6, IC9.16, IC9.29, IC9.39, IC10.1, IC10.2, IC10.3, IC10.4, IC10.7, IC11.2, IC12.4, IC12.PAD, ICSP2.3, J20.3, J21.3, J22.3, J23.3, J24.3, J25.3, JP11.1, LED9.C, LED10.C, LED11.C, LED12.C, LP2.C, R58.2, R60.1, R62.1, SV11.4, SV11.9, SV11.10, SV11.19, SV12.15, SV12.16, U17.2, U18.2, U19.2, U20.2, VR5.2, VR5.4, VR6.2, VR6.4, XT3.2, XT3.4
GND6: JP15.1, JP20.1, JP21.1, JP30.1, JP46.1, JP47.1, UN1.GND@1, UN1.GND@2, UN1.GND@3, UN1.GND@4, UN1.GND@5, UN1.GND@6, UN1.H1, UN1.H2, UN1.H3, UN1.H4, UN1.P_GND
IN_A1: SV1.17, U3.3
IN_A2: SV7.17, U11.3
IN_A3: SV12.17, U19.3
IN_A4: JP48.1, UN1.ANA1
IN_B1: SV1.19, U4.3
IN_B2: SV7.19, U12.3
IN_B3: SV12.19, U20.3
IN_B5: JP50.1, UN1.ANB1
IO0: IC1.35, SV2.12
IO1: IC1.25, SV2.14
IO2: IC1.26, SV2.16
IO3: IC1.27, J4.4, SV2.18
IO4: IC1.36, J5.4, SV2.20
IO5: IC1.34, J3.4, SV2.17
IO6: IC1.33, J2.4, SV2.15
IO7: IC1.43, J6.1
IO8: IC1.32, J7.1
IO9: J9.2, SV4.1
IO10: J8.2, SV4.2
IO18: IC5.32, J12.1
IO19: IC5.43, J11.1
IO20: IC5.36, J16.4, SV6.20
IO21: IC5.27, J15.4, SV6.18
IO22: IC5.26, SV6.16
IO23: IC5.25, SV6.14
IO24: IC5.34, J14.4, SV6.17
IO25: IC5.33, J13.4, SV6.15
IO26: IC5.35, SV6.12
IO27: J18.2, SV9.1
IO28: J17.2, SV9.2
IO36: IC9.32, J21.1
IO37: IC9.43, J20.1
IO38: IC9.36, J25.4, SV11.20
IO39: IC9.27, J24.4, SV11.18
IO40: IC9.26, SV11.16
IO41: IC9.25, SV11.14
IO42: IC9.34, J23.4, SV11.17
IO43: IC9.33, J22.4, SV11.15
IO44: IC9.35, SV11.12
IO45: JP23.1, UN1.IO0
IO46: JP25.1, UN1.IO1
IO47: JP26.1, UN1.IO6
IO48: JP27.1, UN1.IO2
IO49: JP28.1, UN1.IO5
IO50: JP29.1, UN1.IO3
IO51: JP31.1, UN1.IO4
IO52: JP32.1, UN1.IO8
IO54: JP33.1, UN1.IO7
LD1: IC1.2, R4.1
LD2: IC1.3, R5.1
LD3: IC1.4, R6.1
LD4: IC1.5, R8.1
LD5: IC5.3, R30.1
LD6: IC5.2, R29.1
LD7: IC5.5, R32.1
LD8: IC5.4, R31.1
LD9: IC9.3, R54.1
LD10: IC9.2, R53.1
LD11: IC9.5, R56.1
LD12: IC9.4, R55.1
MCLR: IC1.18, ICSP.1, R1.1
MCLR1: IC5.18, ICSP1.1, R26.1
MCLR2: IC9.18, ICSP2.1, R50.1
unnamed: IC3.3, L3.1
unnamed: C7.2, IC1.30, XT1.1
unnamed: C6.1, IC1.31, XT1.3
unnamed: C14.1, IC4.1
unnamed: LP.A, R2.1
unnamed: IC4.7, R9.1
unnamed: IC3.5, R13.1, R14.2
unnamed: C12.1, IC4.8
unnamed: IC4.5, R10.1, R11.1
unnamed: J6.2, SV1.2
unnamed: L4.A, R17.2
unnamed: LED1.A, R4.2
unnamed: LED2.A, R5.2
unnamed: L5.A, R18.2
unnamed: C14.2, IC4.3, L2.1
unnamed: C15.1, IC4.6
unnamed: C15.2, R12.2
unnamed: U5.8, U7.3, U7.4
unnamed: U6.8, U8.3, U8.4
unnamed: PS1.2, R18.1, U7.1, U7.2
unnamed: R15.2, U1.1
unnamed: R16.2, U2.1
unnamed: J7.2, SV1.1
unnamed: PS2.2, R20.1, U8.1, U8.2
unnamed: PS1.1, R17.1, U5.6
unnamed: PS2.1, R19.1, U6.6
unnamed: C25.1, U7.6
unnamed: C26.1, U8.6
unnamed: R21.2, U7.7
unnamed: R23.2, U8.7
unnamed: D1.A, PS3.2
unnamed: C32.2, IC5.30, XT2.1
unnamed: C31.1, IC5.31, XT2.3
unnamed: LED5.A, R29.2
unnamed: LED6.A, R30.2
unnamed: LP1.A, R25.1
unnamed: IC8.7, R33.1
unnamed: C39.1, IC8.8
unnamed: IC8.5, R34.1, R35.1
unnamed: C41.2, IC8.3, L9.1
unnamed: C42.1, IC8.6
unnamed: C42.2, R36.2
unnamed: C41.1, IC8.1
unnamed: IC7.3, L10.1
unnamed: IC7.5, R37.1, R38.2
unnamed: R39.2, U9.1
unnamed: R40.2, U10.1
unnamed: J11.2, SV7.2
unnamed: J12.2, SV7.1
unnamed: L11.A, R41.2
unnamed: L12.A, R42.2
unnamed: U13.8, U15.3, U15.4
unnamed: U14.8, U16.3, U16.4
unnamed: PS4.2, R42.1, U15.1, U15.2
unnamed: PS5.2, R44.1, U16.1, U16.2
unnamed: PS4.1, R41.1, U13.6
unnamed: PS5.1, R43.1, U14.6
unnamed: C53.1, U15.6
unnamed: C54.1, U16.6
unnamed: R45.2, U15.7
unnamed: R47.2, U16.7
unnamed: D2.A, PS6.2
unnamed: C60.2, IC9.30, XT3.1
unnamed: C59.1, IC9.31, XT3.3
unnamed: LED9.A, R53.2
unnamed: LED10.A, R54.2
unnamed: LP2.A, R49.1
unnamed: IC12.7, R57.1
unnamed: C67.1, IC12.8
unnamed: IC12.5, R58.1, R59.1
unnamed: C69.2, IC12.3, L16.1
unnamed: C70.1, IC12.6
unnamed: C70.2, R60.2
unnamed: C69.1, IC12.1
unnamed: IC11.3, L17.1
unnamed: IC11.5, R61.1, R62.2
unnamed: R63.2, U17.1
unnamed: R64.2, U18.1
unnamed: J20.2, SV12.2
unnamed: J21.2, SV12.1
PWMA1: IC1.14, SV1.9
PWMA2: IC1.10, SV1.10
PWMA3: SV4.9, U5.2
PWMA4: SV4.10, U6.2
PWMA5: IC5.14, SV7.9
PWMA6: IC5.10, SV7.10
PWMA7: SV9.9, U13.2
PWMA8: SV9.10, U14.2
PWMA9: IC9.14, SV12.9
PWMA10: IC9.10, SV12.10
PWMA11: JP40.1, UN1.PWMA1
PWMA12: JP41.1, UN1.PWMA2
PWMB1: IC1.15, SV1.11
PWMB2: IC1.11, SV1.12
PWMB3: SV4.11, U5.3
PWMB4: SV4.12, U6.3
PWMB5: IC5.15, SV7.11
PWMB6: IC5.11, SV7.12
PWMB7: SV9.11, U13.3
PWMB8: SV9.12, U14.3
PWMB9: IC9.15, SV12.11
PWMB10: IC9.11, SV12.12
PWMB11: JP42.1, UN1.PWMB1
PWMB12: JP43.1, UN1.PWMB2
RX1: IC1.38, SV2.7
RX2: IC1.24, SV2.11
RX3: JP4.2, SV3.11
RX4: JP3.2, SV3.7
RX5: IC5.24, SV6.11
RX6: IC5.38, SV6.7
RX7: JP9.2, SV8.11
RX8: JP8.2, SV8.7
RX9: IC9.24, SV11.11
RX10: IC9.38, SV11.7
RX11: JP18.1, UN1.RX1
RX12: JP22.1, UN1.RX2
SCL: IC1.44, IC2.6, R3.2, SV2.8
SCL1: JP5.1, SV3.8
SCL2: IC5.44, IC6.6, R28.2, SV6.8
SCL3: JP10.1, SV8.8
SCL4: IC9.44, IC10.6, R52.2, SV11.8
SCL5: JP19.1, UN1.SCL
SDA: IC1.1, IC2.5, R7.2, SV2.6
SDA1: JP5.2, SV3.6
SDA2: IC5.1, IC6.5, R27.2, SV6.6
SDA3: JP10.2, SV8.6
SDA4: IC9.1, IC10.5, R51.2, SV11.6
SDA5: JP17.1, UN1.SDA
TX1: IC1.37, SV2.5
TX2: IC1.23, SV2.13
TX3: JP3.1, SV3.5
TX4: JP4.1, SV3.13
TX5: IC5.37, SV6.5
TX6: IC5.23, SV6.13
TX7: JP8.1, SV8.5
TX8: JP9.1, SV8.13
TX9: IC9.37, SV11.5
TX10: IC9.23, SV11.13
TX11: JP16.1, UN1.TX1
TX13: JP24.1, UN1.TX2
VCAP/VDDCORE: C1.1, IC1.7
VCAP/VDDCORE1: C33.1, IC5.7
VCAP/VDDCORE2: C61.1, IC9.7
VENC: J1.2, SV1.3, SV1.4
VENC1: J8.5, J9.5, SV4.3, SV4.4
VENC1-LD1: L6.A, R19.2
VENC1-LD2: LED7.A, R31.2
VENC1-LD3: LED3.A, R6.2
VENC1-LD4: L13.A, R43.2
VENC1-LD5: LED11.A, R55.2
VENC2: J10.2, SV7.3, SV7.4
VENC2-LD1: L7.A, R20.2
VENC2-LD2: LED8.A, R32.2
VENC2-LD3: L14.A, R44.2
VENC2-LD4: LED4.A, R8.2
VENC2-LD5: LED12.A, R56.2
VENC3: J17.5, J18.5, SV9.3, SV9.4
VENC4: J19.2, SV12.3, SV12.4
VENC5: JP35.1, UN1.VENC@1
VENC6: JP34.1, UN1.VENC@2

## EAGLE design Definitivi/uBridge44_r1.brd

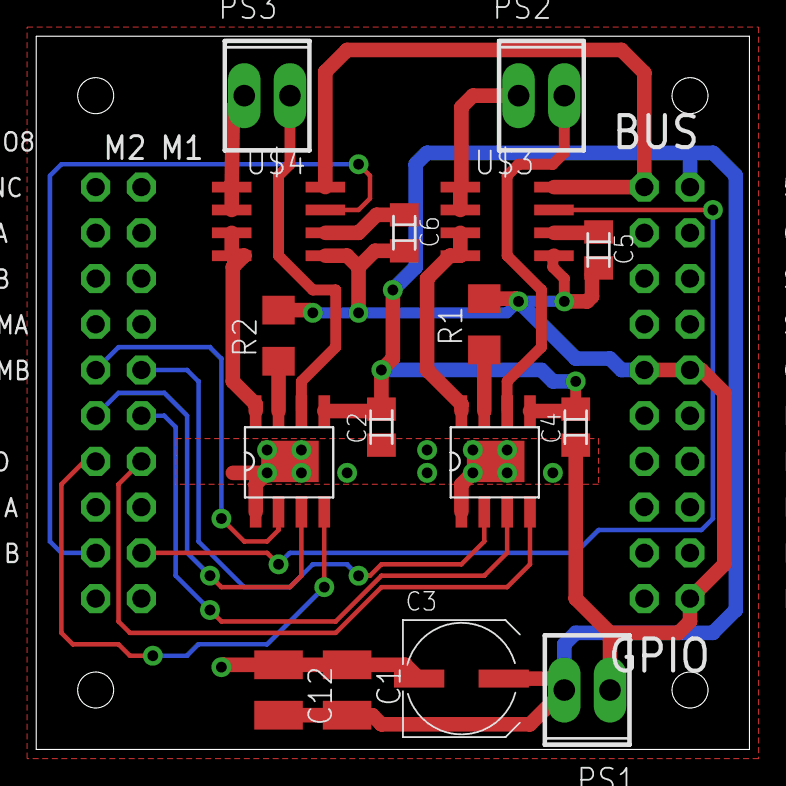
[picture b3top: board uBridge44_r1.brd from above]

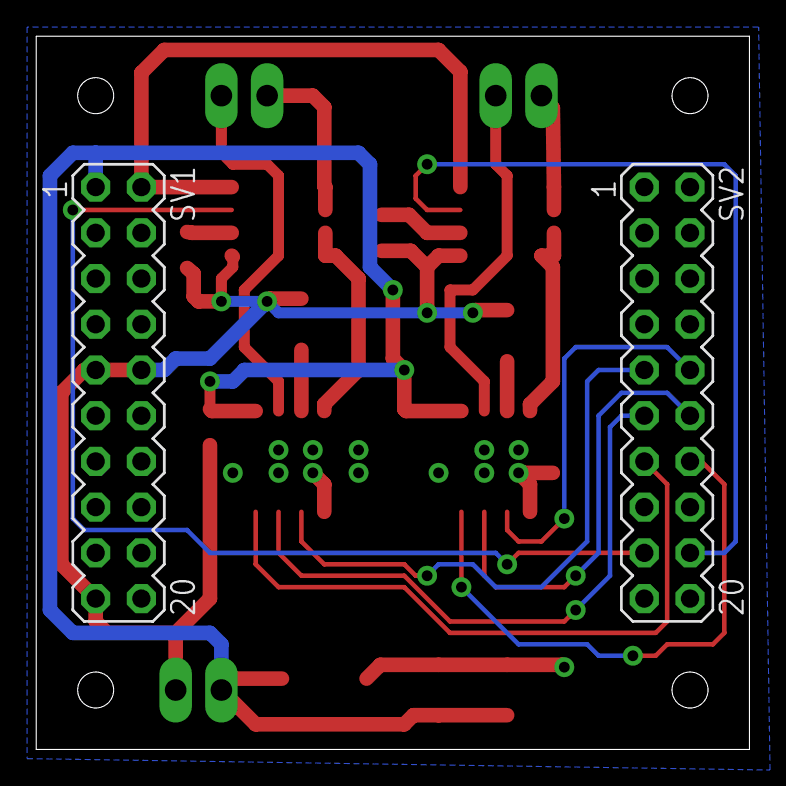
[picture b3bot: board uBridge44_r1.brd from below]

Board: 2 copper layers, 39.6 x 39.6 mm, 18 parts (2 on the bottom side), 21 nets.

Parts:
C1, C12: 10uF/S6 50V; C3225
C2, C4: 220nF; C0805K
C3: PCE4554CT-ND; UD-6,3X7,7_NICHICON
C5, C6: 1nF; C0805K
PS1, PS2, PS3: 2POL254
R1, R2: 0R25; R1206
SV1, SV2: MA10-2
U$1, U$2: A4950; SOICN
U$3, U$4: ACS723; SO08

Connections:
+5V: SV1.2, U$3.8, U$4.8
+12V: C1.2, C2.2, C3.+, C4.2, C12.2, PS1.2, SV1.1, U$1.5VCC, U$2.5VCC
ANA1: SV2.17, U$3.7
ANA2: SV2.18, U$4.7
EN1: SV2.13, U$1.4CS
EN2: SV2.14, U$2.4CS
GND: C1.1, C2.1, C3.-, C4.1, C5.2, C6.2, C12.1, PS1.1, R1.2, R2.2, SV1.4, SV1.9, SV1.10, SV1.19, SV2.15, SV2.16, U$1.1VIN, U$1.PAD, U$2.1VIN, U$2.PAD, U$3.5, U$4.5
unnamed: R2.1, U$2.7BOOT
unnamed: PS3.2, U$2.6GND
unnamed: U$2.8SW, U$4.3, U$4.4
unnamed: C5.1, U$3.6
unnamed: C6.1, U$4.6
unnamed: PS2.1, U$3.1, U$3.2
unnamed: PS2.2, U$1.6GND
unnamed: PS3.1, U$4.1, U$4.2
unnamed: R1.1, U$1.7BOOT
unnamed: U$1.8SW, U$3.3, U$3.4
PWMA1: SV2.9, U$1.2TON
PWMA2: SV2.10, U$2.2TON
PWMB1: SV2.11, U$1.3EN
PWMB2: SV2.12, U$2.3EN

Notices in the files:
parts and their libraries:
SparkFun-Passives: Licensing: Creative Commons ShareAlike 4.0 International - https://creativecommons.org/licenses/by-sa/4.0
